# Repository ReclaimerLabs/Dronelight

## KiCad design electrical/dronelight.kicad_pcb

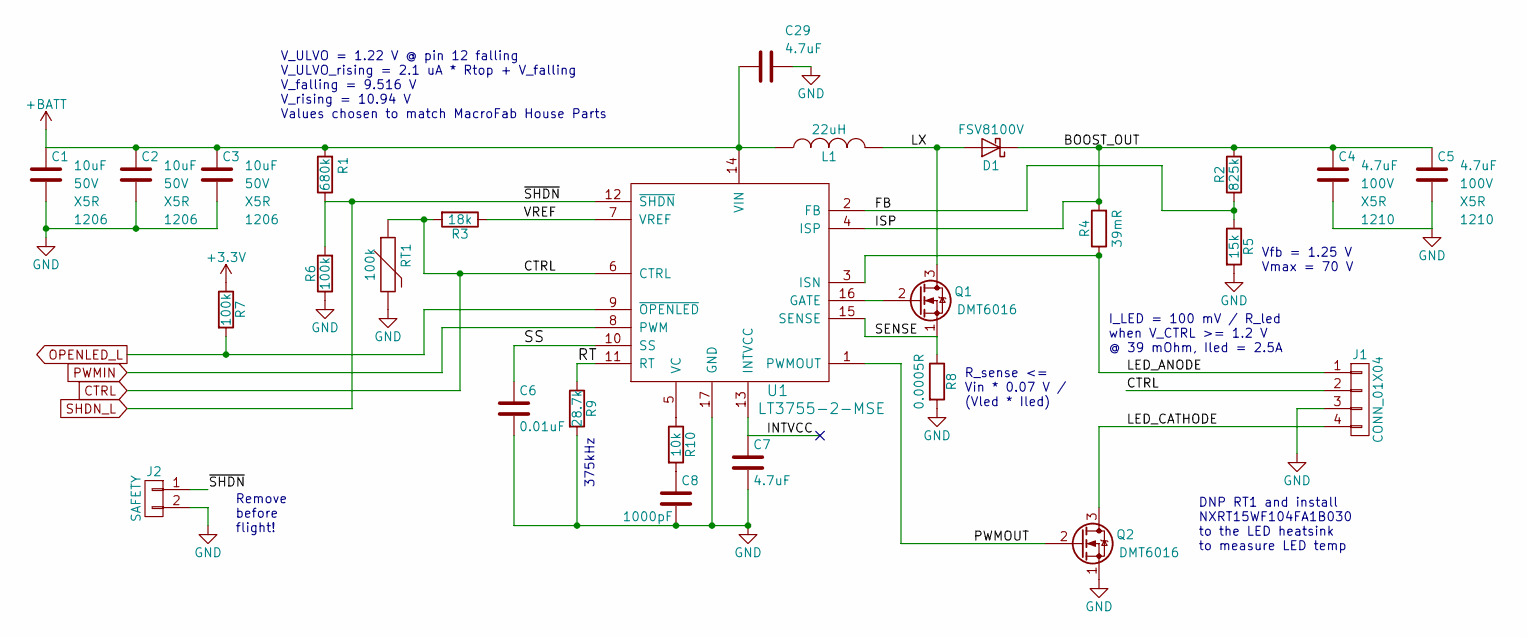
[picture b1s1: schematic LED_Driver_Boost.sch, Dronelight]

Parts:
C1, C2, C3: 10uF; C_1206; Voltage 50V; Manufacturer Part Number CL31A106MBHNNNE
C4, C5: 4.7uF; C_1206; Voltage 100V; Manufacturer Part Number HMK325BJ475KM-PE
C6: 0.01uF; C_0603; Manufacturer Part Number MF-CAP-0603-0.01uF
C7, C29: 4.7uF; C_0805; Manufacturer Part Number CL21A475KOFNNNE
C8: 1000pF; C_0603; Manufacturer Part Number MF-CAP-0603-1nF
D1: FSV8100V; TO-277_3L_Diode; Manufacturer Part Number FSV8100V
J1: CONN_01X04; Header_04x01_2.5mm_RA; Manufacturer Part Number S4B-EH(LF)(SN)
J2: SAFETY; Socket_Strip_Straight_1x02_Pitch2.54mm; Manufacturer Part Number MF-CON-2.54mm-01x02
L1: 22uH; Inductor_DR127; Manufacturer Part Number DR127-220-R
Q1, Q2: DMT6016; POWERDI5060-8; Manufacturer Part Number DMT6016LPS-13
R1: 680k; R_0603; Manufacturer Part Number MF-RES-0603-680K
R2: 825k; R_0603; Manufacturer Part Number MF-RES-0603-825K
R3: 18k; R_0603; Manufacturer Part Number MF-RES-0603-18K
R4: 39mR; R_0603; Manufacturer Part Number ERJ-3BWFR039V
R5: 15k; R_0603; Manufacturer Part Number MF-RES-0603-15K
R6, R7: 100k; R_0603; Manufacturer Part Number MF-RES-0603-100K
R8: 0.0005R; CST0612; Manufacturer Part Number CST0612-FC-R0005-E
R9: 28.7k; R_0603; Manufacturer Part Number ERJ-3EKF2872V
R10: 10k; R_0603; Manufacturer Part Number MF-RES-0603-10K
RT1: 100k; R_0603; Manufacturer Part Number NCP18WF104J03RB
U1: LT3755-2-MSE; MSOP-16-1EP_3x4mm_Pitch0.5mm; Manufacturer Part Number LT3755EMSE-2#PBF

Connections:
+3V3: R7.1; also elsewhere on the board
+BATT: C1.1, C2.1, C3.1, C29.2, L1.1, R1.2, U1.14 (VIN); also elsewhere on the board
/LED Driver Boost/BOOST_OUT: C4.1, C5.1, D1.1 (K), R2.2, R4.2, U1.4 (ISP)
/LED Driver Boost/FB: R2.1, R5.1, U1.2 (FB)
/LED Driver Boost/INTVCC: C7.1, U1.13 (INTVCC)
/LED Driver Boost/LED_ANODE: J1.1, R4.1, U1.3 (ISN)
/LED Driver Boost/LED_CATHODE: J1.4, Q2.3 (D)
/LED Driver Boost/LX: D1.2 (A), L1.2, Q1.3 (D)
/LED Driver Boost/PWMOUT: Q2.2 (G), U1.1 (PWMOUT)
/LED Driver Boost/RT: R9.1, U1.11 (RT)
/LED Driver Boost/SENSE: Q1.1 (S), R8.1, U1.15 (SENSE)
/LED Driver Boost/SS: C6.1, U1.10 (SS)
/LED Driver Boost/VREF: R3.1, U1.7 (VREF)
CTRL: J1.2, R3.2, RT1.1, U1.6 (CTRL); also elsewhere on the board
GND: C1.2, C2.2, C3.2, C4.2, C5.2, C6.2, C7.2, C8.2, C29.1, J1.3, J2.2, Q2.1 (S), R5.2, R6.1, R8.2, R9.2, RT1.2, U1.17 (GND); also elsewhere on the board
unnamed: C8.1, R10.2
unnamed: Q1.2 (G), U1.16 (GATE)
unnamed: R10.1, U1.5 (VC)
OPENLED_L: R7.2, U1.9 (~OPENLED); also elsewhere on the board
PWMIN: U1.8 (PWM); also elsewhere on the board
SHDN_L: J2.1, R1.1, R6.2, U1.12 (~SHDN); also elsewhere on the board

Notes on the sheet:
375kHz
Vfb = 1.25 V Vmax = 70 V
Remove before flight!
V_ULVO = 1.22 V @ pin 12 falling V_ULVO_rising = 2.1 uA * Rtop + V_falling V_falling = 9.516 V V_rising = 10.94 V Values chosen to match MacroFab House Parts
DNP RT1 and install NXRT15WF104FA1B030 to the LED heatsink to measure LED temp
I_LED = 100 mV / R_led when V_CTRL >= 1.2 V @ 39 mOhm, Iled = 2.5A
R_sense <= Vin * 0.07 V / (Vled * Iled)

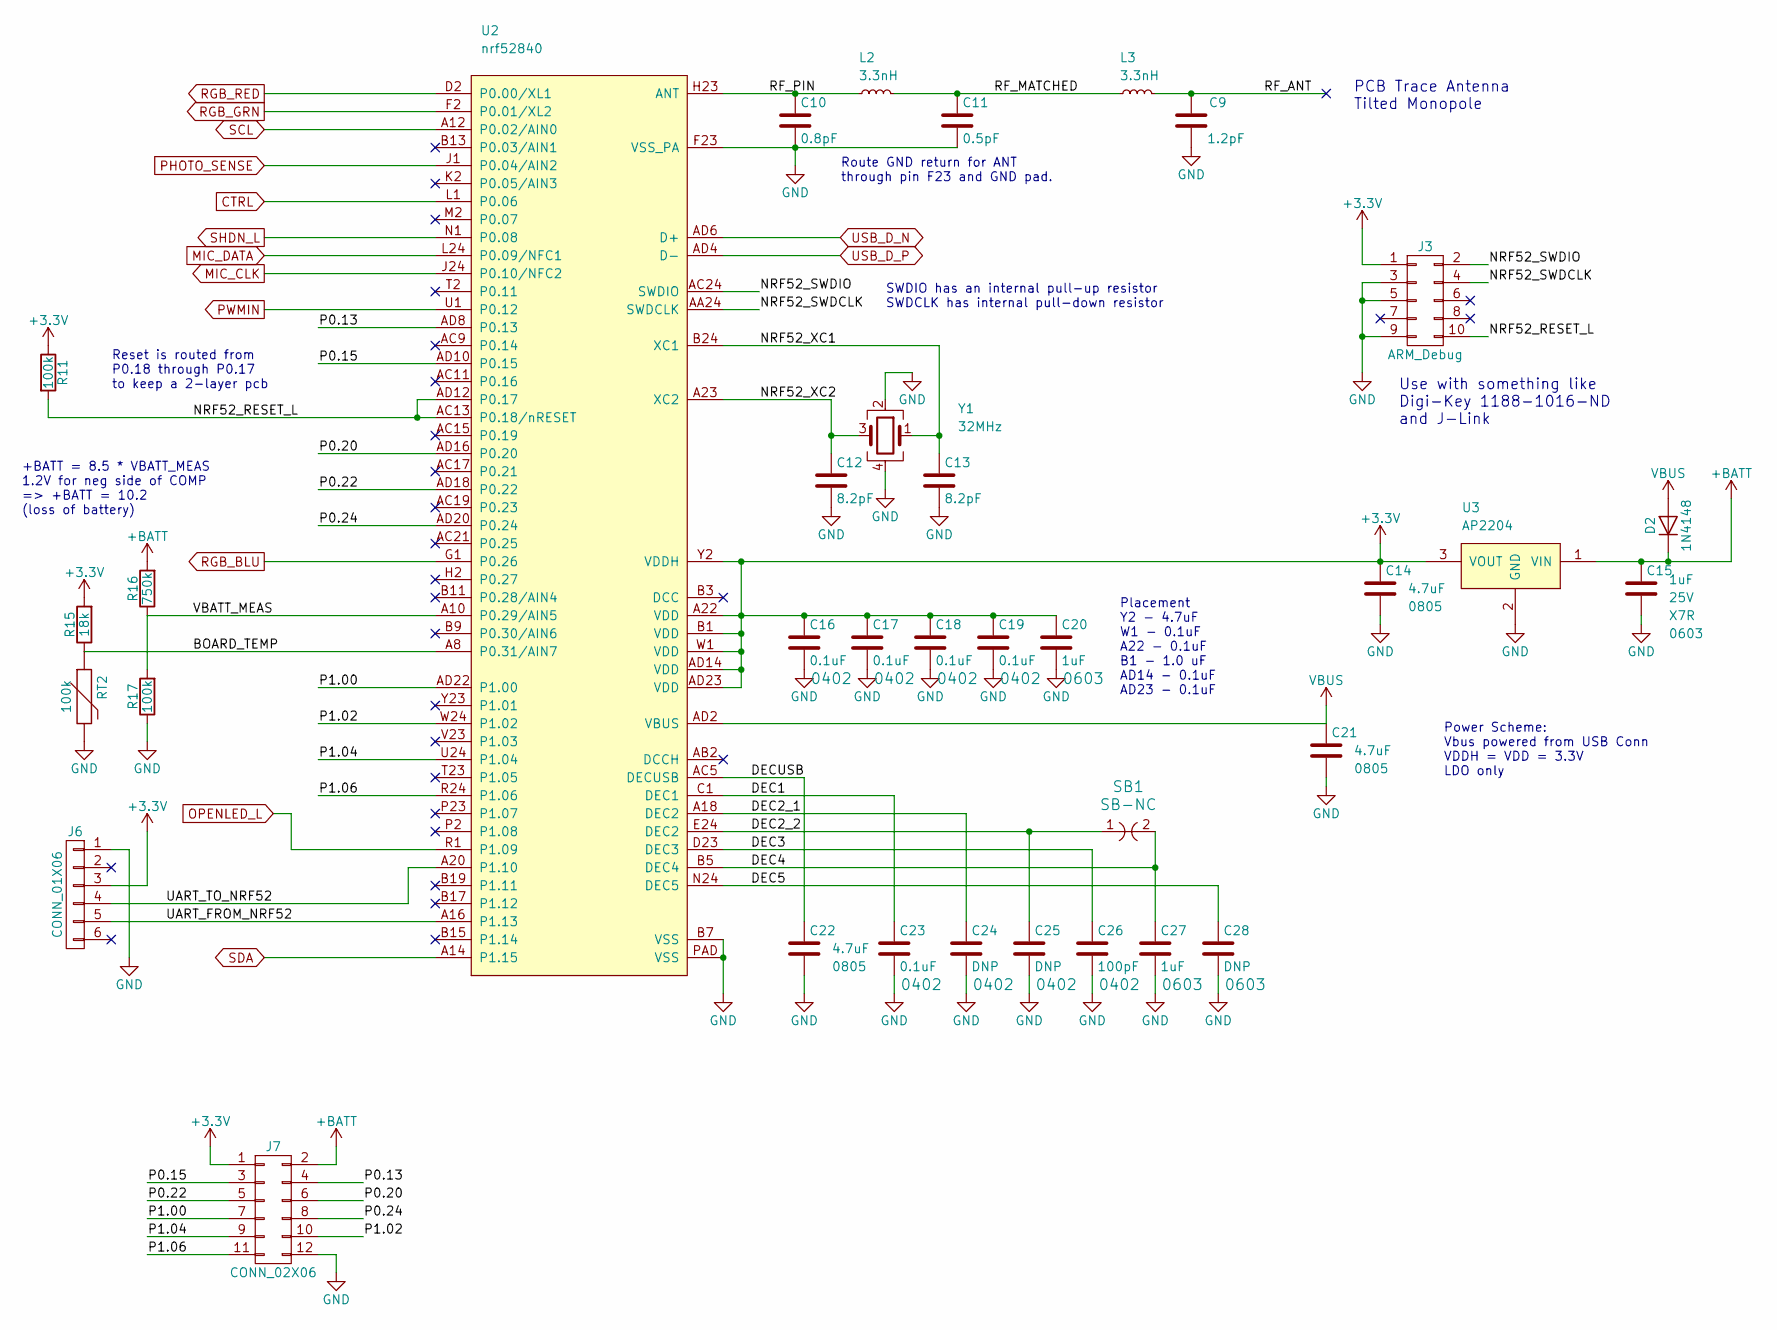
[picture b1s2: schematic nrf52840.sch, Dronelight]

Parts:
C9: 1.2pF; C_0402; Manufacturer Part Number 500R07S1R2BV4T
C10: 0.8pF; C_0402; Manufacturer Part Number GRM1555C2AR80BA01D
C11: 0.5pF; C_0402; Manufacturer Part Number GRM1555C1HR50BA01D
C12, C13: 8.2pF; C_0402; Manufacturer Part Number MF-CAP-0402-8.2pF
C14, C21, C22: 4.7uF; C_0805; Manufacturer Part Number CL21A475KOFNNNE
C15: 1uF; C_0603; Voltage 25V; Manufacturer Part Number MF-CAP-0603-1uF
C16, C17, C18, C19, C23: 0.1uF; C_0402; Manufacturer Part Number MF-CAP-0402-0.1uF
C20, C27: 1uF; C_0603; Manufacturer Part Number MF-CAP-0603-1uF
C24, C25: DNP; C_0402; Manufacturer Part Number MF-CAP-0402-0.1uF
C26: 100pF; C_0402; Manufacturer Part Number GRM1555C1H101JA01D
C28: DNP; C_0603; Manufacturer Part Number MF-CAP-0603-1uF
D2: 1N4148; D_SOD-123; Manufacturer Part Number MF-DIO-SOD123-1N4148
J3: ARM_Debug; HEADER_SMT_02x05_1.27MM_POL; Manufacturer Part Number 3220-10-0300-00
J6: CONN_01X06; Socket_Strip_Straight_1x06_Pitch2.54mm; Manufacturer Part Number MF-CON-2.54mm-01x06
J7: CONN_02X06; Socket_Strip_Straight_2x06_Pitch2.54mm
L2, L3: 3.3nH; C_0402; Manufacturer Part Number MLG1005S3N3BT000
R11, R17: 100k; R_0603; Manufacturer Part Number MF-RES-0603-100K
R15: 18k; R_0603; Manufacturer Part Number MF-RES-0603-18K
R16: 750k; R_0603; Manufacturer Part Number MF-RES-0603-750K
RT2: 100k; R_0603; Manufacturer Part Number NCP18WF104J03RB
SB1: SB-NC
U2: nrf52840; AQFN73; Manufacturer Part Number NRF52840-QIAA-T
U3: AP2204; SOT89-3; Manufacturer Part Number AP2204R-3.3TRG1
Y1: 32MHz; Crystal_SMD_2016-4pin_2.0x1.6mm; Manufacturer Part Number XRCGB32M000F2P00R0

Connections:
+3V3: C14.1, C16.1, C17.1, C18.1, C19.1, C20.1, J3.1, J6.3, J7.1, R11.1, R15.2, U2.A22 (VDD), U2.AD14 (VDD), U2.AD23 (VDD), U2.B1 (VDD), U2.W1 (VDD), U2.Y2 (VDDH), U3.3 (VOUT); also elsewhere on the board
+BATT: C15.1, D2.1 (K), J7.2, R16.2, U3.1 (VIN); also elsewhere on the board
/nrf52840/BOARD_TEMP: R15.1, RT2.1, U2.A8 (P0.31/AIN7)
/nrf52840/DEC1: C23.1, U2.C1 (DEC1)
/nrf52840/DEC2_1: C24.1, U2.A18 (DEC2)
/nrf52840/DEC2_2: C25.1, SB1.1, U2.E24 (DEC2)
/nrf52840/DEC3: C26.1, U2.D23 (DEC3)
/nrf52840/DEC4: C27.1, SB1.2, U2.B5 (DEC4)
/nrf52840/DEC5: C28.1, U2.N24 (DEC5)
/nrf52840/DECUSB: C22.1, U2.AC5 (DECUSB)
/nrf52840/NRF52_RESET_L: J3.10, R11.2, U2.AC13 (P0.18/nRESET), U2.AD12 (P0.17)
/nrf52840/NRF52_SWDCLK: J3.4, U2.AA24 (SWDCLK)
/nrf52840/NRF52_SWDIO: J3.2, U2.AC24 (SWDIO)
/nrf52840/NRF52_XC1: C13.1, U2.B24 (XC1), Y1.1
/nrf52840/NRF52_XC2: C12.1, U2.A23 (XC2), Y1.3
/nrf52840/P0.13: J7.4, U2.AD8 (P0.13)
/nrf52840/P0.15: J7.3, U2.AD10 (P0.15)
/nrf52840/P0.20: J7.6, U2.AD16 (P0.20)
/nrf52840/P0.22: J7.5, U2.AD18 (P0.22)
/nrf52840/P0.24: J7.8, U2.AD20 (P0.24)
/nrf52840/P1.00: J7.7, U2.AD22 (P1.00)
/nrf52840/P1.02: J7.10, U2.W24 (P1.02)
/nrf52840/P1.04: J7.9, U2.U24 (P1.04)
/nrf52840/P1.06: J7.11, U2.R24 (P1.06)
/nrf52840/RF_ANT: C9.2, L3.2
/nrf52840/RF_MATCHED: C11.1, L2.2, L3.1
/nrf52840/RF_PIN: C10.1, L2.1, U2.H23 (ANT)
/nrf52840/UART_FROM_NRF52: J6.5, U2.A16 (P1.13)
/nrf52840/UART_TO_NRF52: J6.4, U2.A20 (P1.10)
/nrf52840/VBATT_MEAS: R16.1, R17.2, U2.A10 (P0.29/AIN5)
CTRL: U2.L1 (P0.06); also elsewhere on the board
GND: C9.1, C10.2, C11.2, C12.2, C13.2, C14.2, C15.2, C16.2, C17.2, C18.2, C19.2, C20.2, C21.2, C22.2, C23.2, C24.2, C25.2, C26.2, C27.2, C28.2, J3.3, J3.5, J3.9, J6.1, J7.12, R17.1, RT2.2, U2.B7 (VSS), U2.F23 (VSS_PA), U2.PAD (VSS), U3.2 (GND), Y1.2, Y1.4; also elsewhere on the board
MIC_CLK: U2.J24 (P0.10/NFC2); also elsewhere on the board
MIC_DATA: U2.L24 (P0.09/NFC1); also elsewhere on the board
OPENLED_L: U2.R1 (P1.09); also elsewhere on the board
PHOTO_SENSE: U2.J1 (P0.04/AIN2); also elsewhere on the board
PWMIN: U2.U1 (P0.12); also elsewhere on the board
RGB_BLU: U2.G1 (P0.26); also elsewhere on the board
RGB_GRN: U2.F2 (P0.01/XL2); also elsewhere on the board
RGB_RED: U2.D2 (P0.00/XL1); also elsewhere on the board
SCL: U2.A12 (P0.02/AIN0); also elsewhere on the board
SDA: U2.A14 (P1.15); also elsewhere on the board
SHDN_L: U2.N1 (P0.08); also elsewhere on the board
USB_D_N: U2.AD6 (D+); also elsewhere on the board
USB_D_P: U2.AD4 (D-); also elsewhere on the board
VBUS: C21.1, D2.2 (A), U2.AD2 (VBUS); also elsewhere on the board

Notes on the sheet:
Use with something like Digi-Key 1188-1016-ND and J-Link
SWDIO has an internal pull-up resistor SWDCLK has internal pull-down resistor
Route GND return for ANT through pin F23 and GND pad.
Placement Y2 - 4.7uF W1 - 0.1uF A22 - 0.1uF B1 - 1.0 uF AD14 - 0.1uF AD23 - 0.1uF
Power Scheme: Vbus powered from USB Conn VDDH = VDD = 3.3V LDO only
+BATT = 8.5 * VBATT_MEAS 1.2V for neg side of COMP => +BATT = 10.2 (loss of battery)
Reset is routed from P0.18 through P0.17 to keep a 2-layer pcb
PCB Trace Antenna Tilted Monopole

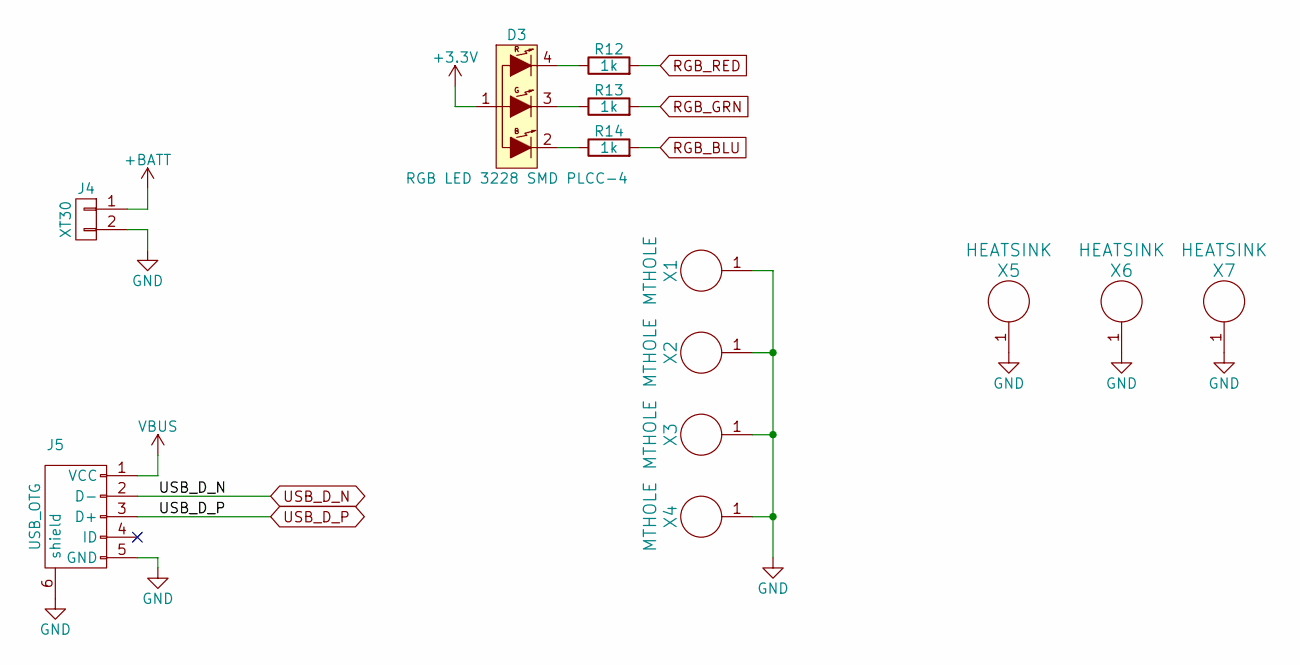
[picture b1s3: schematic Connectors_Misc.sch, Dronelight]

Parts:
D3: RGB LED 3228 SMD PLCC-4; PLCC4; Manufacturer Part Number MF-LED-3228-RGB
J4: XT30
J5: USB_OTG; USB_Micro-B_10118194-0001LF; Manufacturer Part Number MF-CON-MICROUSB-RIGHT
R12, R13, R14: 1k; R_0603; Manufacturer Part Number MF-RES-0603-1K
X1, X2, X3, X4: MTHOLE; MountingHole_3.5mm_Pad_Via
X5, X6, X7: HEATSINK; 573100D00010G; Manufacturer Part Number 573100D00010G

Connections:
+3V3: D3.1; also elsewhere on the board
+BATT: J4.1; also elsewhere on the board
GND: J4.2, J5.5 (GND), J5.6 (shield), X1.1, X2.1, X3.1, X4.1, X5.1, X6.1, X7.1; also elsewhere on the board
unnamed: D3.2 (B), R14.1
unnamed: D3.3 (G), R13.1
unnamed: D3.4 (R), R12.1
RGB_BLU: R14.2; also elsewhere on the board
RGB_GRN: R13.2; also elsewhere on the board
RGB_RED: R12.2; also elsewhere on the board
USB_D_N: J5.2 (D-); also elsewhere on the board
USB_D_P: J5.3 (D+); also elsewhere on the board
VBUS: J5.1 (VCC); also elsewhere on the board

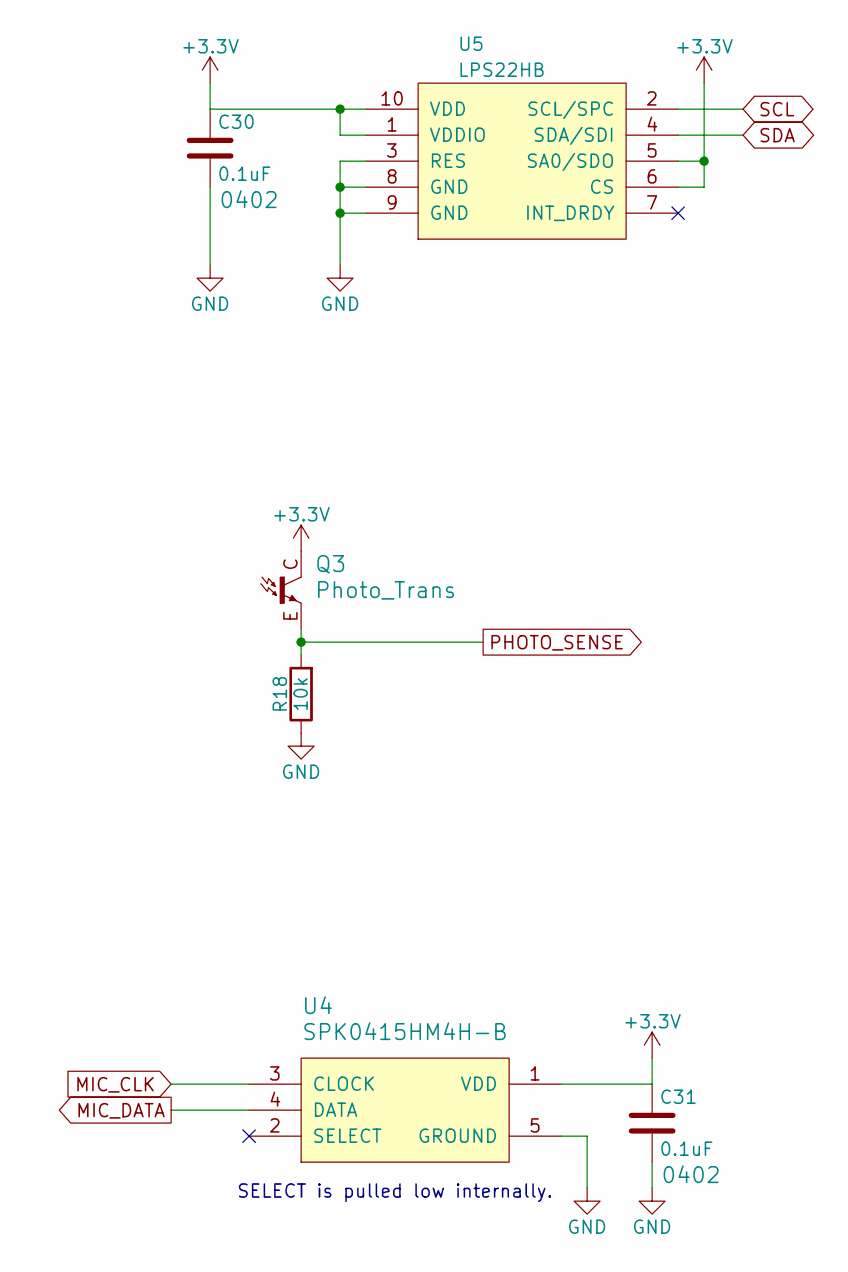
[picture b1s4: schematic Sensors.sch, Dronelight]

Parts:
C30, C31: 0.1uF; C_0402; Manufacturer Part Number MF-CAP-0402-0.1uF
Q3: Photo_Trans; Photo_Trans_ALS-PT19-315C; Manufacturer Part Number ALS-PT19-315C/L177/TR8
R18: 10k; R_0603; Manufacturer Part Number MF-RES-0603-10K
U4: SPK0415HM4H-B; SPK0415HM4H-8; Manufacturer Part Number SPK0415HM4H-B-7
U5: LPS22HB; LGA10R50P2X3_200X200X80; Manufacturer Part Number LPS22HBTR

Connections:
+3V3: C30.1, C31.1, Q3.C, U4.1 (VDD), U5.1 (VDDIO), U5.5 (SA0/SDO), U5.6 (CS), U5.10 (VDD); also elsewhere on the board
GND: C30.2, C31.2, R18.1, U4.5 (GROUND), U5.3 (RES), U5.8 (GND), U5.9 (GND); also elsewhere on the board
MIC_CLK: U4.3 (CLOCK); also elsewhere on the board
MIC_DATA: U4.4 (DATA); also elsewhere on the board
PHOTO_SENSE: Q3.E, R18.2; also elsewhere on the board
SCL: U5.2 (SCL/SPC); also elsewhere on the board
SDA: U5.4 (SDA/SDI); also elsewhere on the board

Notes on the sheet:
SELECT is pulled low internally.

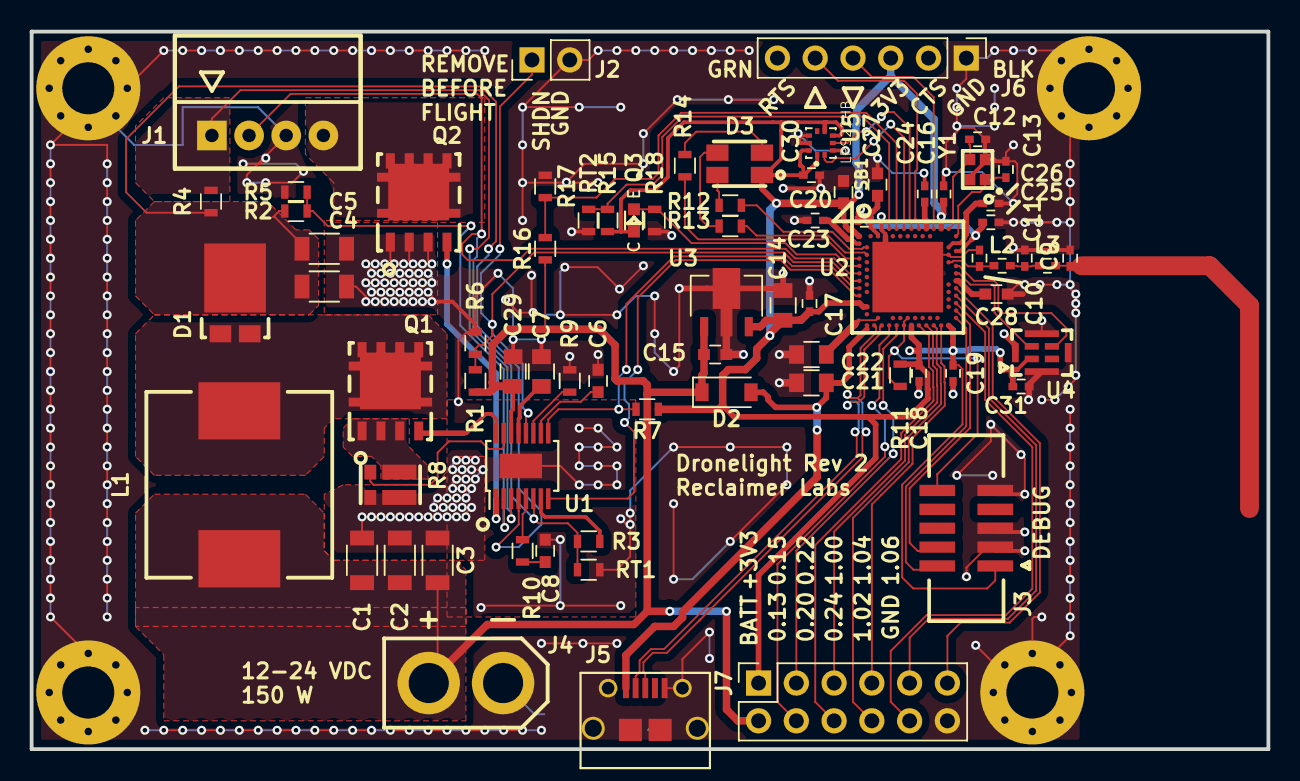
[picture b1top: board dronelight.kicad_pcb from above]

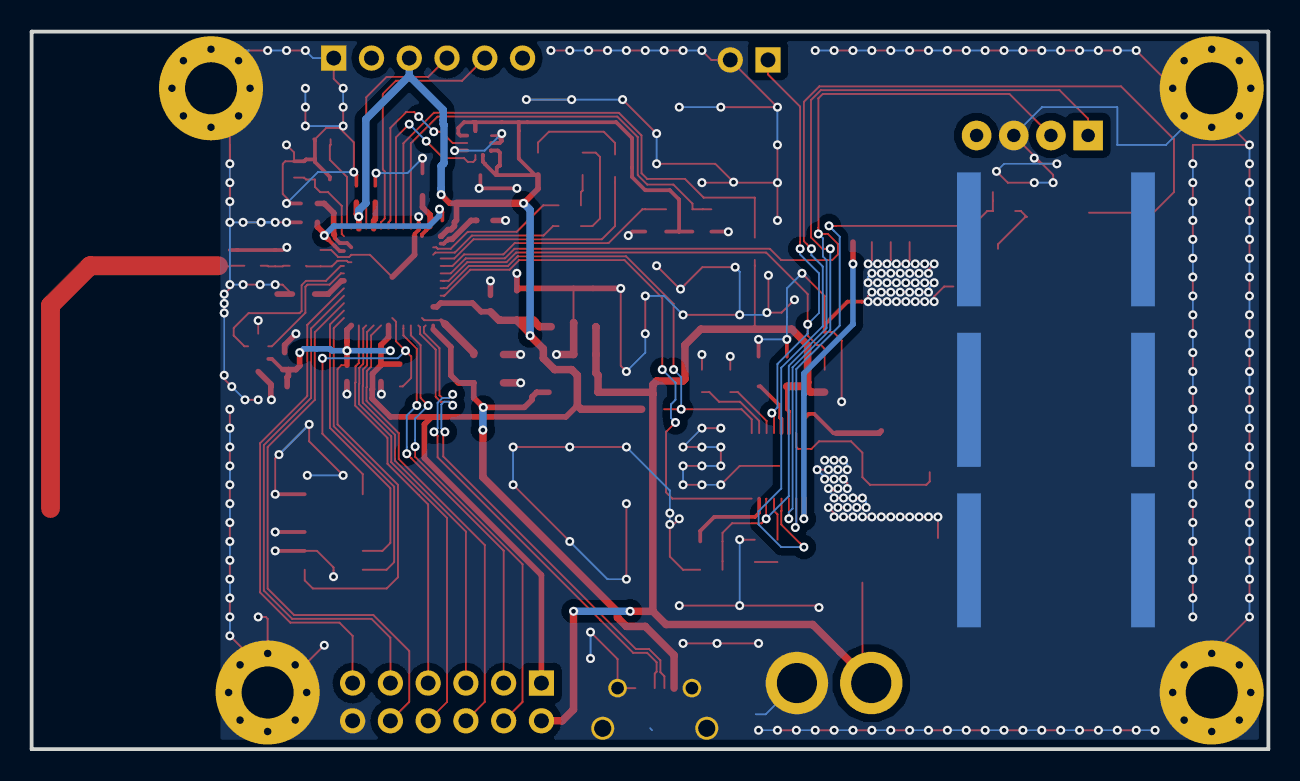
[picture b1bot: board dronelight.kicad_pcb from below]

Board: 2 copper layers, 83.2 x 48.3 mm, 81 parts (3 on the bottom side), 63 nets.

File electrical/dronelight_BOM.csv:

Reference, Value, Footprint, Datasheet, Manufacturer, Manufacturer Part Number, Supplier 1, Supplier 1 Part Number, Voltage, DisplayFootprint, TempCo, DNP
"D1","FSV8100V","Reclaimer_Labs:TO-277_3L_Diode","","Fairchild-ON","FSV8100V","Digikey","FSV8100VCT-ND","","","",""
"L1","22uH","Reclaimer_Labs:Inductor_DR127","","Eaton","DR127-220-R","Digikey","513-1044-1-ND","","","",""
"U1","LT3755-2-MSE","Housings_SSOP:MSOP-16-1EP_3x4mm_Pitch0.5mm","","Linear","LT3755EMSE-2#PBF","Digikey","LT3755EMSE-2#PBF-ND","","","",""
"Q1","DMT6016","Reclaimer_Labs:POWERDI5060-8","","Diodes Inc","DMT6016LPS-13","","","","","",""
"R8","0.0005R","Reclaimer_Labs:CST0612","","Bourns","CST0612-FC-R0005-E","","","","","",""
"C7","4.7uF","Capacitors_SMD:C_0805","","Samsung","CL21A475KOFNNNE","","","","","",""
"C8","1000pF","Capacitors_SMD:C_0603","","MacroFab","MF-CAP-0603-1nF","","","","","",""
"R9","28.7k","Resistors_SMD:R_0603","","Panasonic","ERJ-3EKF2872V","Digikey","P28.7KHCT-ND","","","",""
"C6","0.01uF","Capacitors_SMD:C_0603","","MacroFab","MF-CAP-0603-0.01uF","","","","","",""
"R7","100k","Resistors_SMD:R_0603","","MacroFab","MF-RES-0603-100K","","","","","",""
"RT1","100k","Resistors_SMD:R_0603","","Murata","NCP18WF104J03RB","Digikey","490-2430-1-ND","","","",""
"R3","18k","Resistors_SMD:R_0603","","MacroFab","MF-RES-0603-18K","","","","","",""
"R6","100k","Resistors_SMD:R_0603","","MacroFab","MF-RES-0603-100K","","","","","",""
"R1","680k","Resistors_SMD:R_0603","","MacroFab","MF-RES-0603-680K","","","","","",""
"C3","10uF","Capacitors_SMD:C_1206","","Samsung","CL31A106MBHNNNE","","","50V","1206","X5R",""
"R10","10k","Resistors_SMD:R_0603","","MacroFab","MF-RES-0603-10K","","","","","",""
"R2","825k","Resistors_SMD:R_0603","","MacroFab","MF-RES-0603-825K","","","","","",""
"R4","39mR","Resistors_SMD:R_0603","","Panasonic","ERJ-3BWFR039V","","","","","",""
"R5","15k","Resistors_SMD:R_0603","","MacroFab","MF-RES-0603-15K","","","","","",""
"J2","SAFETY","Socket_Strips:Socket_Strip_Straight_1x02_Pitch2.54mm","","MacroFab","MF-CON-2.54mm-01x02","","","","","",""
"J1","CONN_01X04","Reclaimer_Labs:Header_04x01_2.5mm_RA","","JST","S4B-EH(LF)(SN)","","","","","",""
"C2","10uF","Capacitors_SMD:C_1206","","Samsung","CL31A106MBHNNNE","","","50V","1206","X5R",""
"C1","10uF","Capacitors_SMD:C_1206","","Samsung","CL31A106MBHNNNE","","","50V","1206","X5R",""
"C4","4.7uF","Capacitors_SMD:C_1206","","Taiyo Yuden","HMK325BJ475KM-PE","","","100V","1210","X5R",""
"C5","4.7uF","Capacitors_SMD:C_1206","","Taiyo Yuden","HMK325BJ475KM-PE","","","100V","1210","X5R",""
"Q2","DMT6016","Reclaimer_Labs:POWERDI5060-8","","Diodes Inc","DMT6016LPS-13","","","","","",""
"C29","4.7uF","Capacitors_SMD:C_0805","","Samsung","CL21A475KOFNNNE","","","","","",""
"U2","nrf52840","Reclaimer_Labs:AQFN73","","Nordic","NRF52840-QIAA-T","","","","","",""
"J3","ARM_Debug","Reclaimer_Labs:HEADER_SMT_02x05_1.27MM_POL","","CNC Tech","3220-10-0300-00","","","","","",""
"R11","100k","Resistors_SMD:R_0603","","MacroFab","MF-RES-0603-100K","","","","","",""
"Y1","32MHz","Reclaimer_Labs:Crystal_SMD_2016-4pin_2.0x1.6mm","","Murata","XRCGB32M000F2P00R0","","","","","",""
"C12","8.2pF","Capacitors_SMD:C_0402","","MacroFab","MF-CAP-0402-8.2pF","","","","","",""
"C13","8.2pF","Capacitors_SMD:C_0402","","MacroFab","MF-CAP-0402-8.2pF","","","","","",""
"C10","0.8pF","Capacitors_SMD:C_0402","","Murata","GRM1555C2AR80BA01D","","","","","",""
"L2","3.3nH","Capacitors_SMD:C_0402","","TDK","MLG1005S3N3BT000","","","","","",""
"C11","0.5pF","Capacitors_SMD:C_0402","","Murata","GRM1555C1HR50BA01D","","","","","",""
"D2","1N4148","Diodes_SMD:D_SOD-123","","MacroFab","MF-DIO-SOD123-1N4148","","","","","",""
"C15","1uF","Capacitors_SMD:C_0603","","MacroFab","MF-CAP-0603-1uF","","","25V","0603","X7R",""
"U3","AP2204","Reclaimer_Labs:SOT89-3","","Diodes Inc","AP2204R-3.3TRG1","","","","","",""
"C16","0.1uF","Capacitors_SMD:C_0402","","MacroFab","MF-CAP-0402-0.1uF","","","","0402","",""
"C20","1uF","Capacitors_SMD:C_0603","","MacroFab","MF-CAP-0603-1uF","","","","0603","",""
"C17","0.1uF","Capacitors_SMD:C_0402","","MacroFab","MF-CAP-0402-0.1uF","","","","0402","",""
"C18","0.1uF","Capacitors_SMD:C_0402","","MacroFab","MF-CAP-0402-0.1uF","","","","0402","",""
"C19","0.1uF","Capacitors_SMD:C_0402","","MacroFab","MF-CAP-0402-0.1uF","","","","0402","",""
"C23","0.1uF","Capacitors_SMD:C_0402","","MacroFab","MF-CAP-0402-0.1uF","","","","0402","",""
"C26","100pF","Capacitors_SMD:C_0402","","Murata","GRM1555C1H101JA01D","","","","0402","",""
"C27","1uF","Capacitors_SMD:C_0603","","MacroFab","MF-CAP-0603-1uF","","","","0603","",""
"C24","DNP","Capacitors_SMD:C_0402","","MacroFab","MF-CAP-0402-0.1uF","","","","0402","","DNP"
"C25","DNP","Capacitors_SMD:C_0402","","MacroFab","MF-CAP-0402-0.1uF","","","","0402","","DNP"
"A1","Antenna","Reclaimer_Labs:2450AT18B100E","","Johanson","2450AT18B100E","","","","","",""
"L3","3.3nH","Capacitors_SMD:C_0402","","TDK","MLG1005S3N3BT000","","","","","",""
"C9","1.2pF","Capacitors_SMD:C_0402","","Johanson","500R07S1R2BV4T","","","","","",""
"L4","2.7nH","Capacitors_SMD:C_0402","","Johanson","L-07C2N7SV6T","","","","","",""
"J6","CONN_01X06","Socket_Strips:Socket_Strip_Straight_1x06_Pitch2.54mm","","MacroFab","MF-CON-2.54mm-01x06","","","","","",""
"C21","4.7uF","Capacitors_SMD:C_0805","","Samsung","CL21A475KOFNNNE","","","","0805","",""
"C14","4.7uF","Capacitors_SMD:C_0805","","Samsung","CL21A475KOFNNNE","","","","0805","",""
"C22","4.7uF","Capacitors_SMD:C_0805","","Samsung","CL21A475KOFNNNE","","","","0805","",""
"RT2","100k","Resistors_SMD:R_0603","","Murata","NCP18WF104J03RB","Digikey","490-2430-1-ND","","","",""
"R15","18k","Resistors_SMD:R_0603","","MacroFab","MF-RES-0603-18K","","","","","",""
"R16","750k","Resistors_SMD:R_0603","","MacroFab","MF-RES-0603-750K","","","","","",""
"R17","100k","Resistors_SMD:R_0603","","MacroFab","MF-RES-0603-100K","","","","","",""
"J7","CONN_02X06","Socket_Strips:Socket_Strip_Straight_2x06_Pitch2.54mm",""
"C28","DNP","Capacitors_SMD:C_0603","","MacroFab","MF-CAP-0603-1uF","","","","0603","","DNP"
"J4","XT30","Reclaimer_Labs:XT30",""
"J5","USB_OTG","Reclaimer_Labs:USB_Micro-B_10118194-0001LF","","MacroFab","MF-CON-MICROUSB-RIGHT","","","","","",""
"X1","MTHOLE","Reclaimer_Labs:MountingHole_3.5mm_Pad_Via",""
"R12","1k","Resistors_SMD:R_0603","","MacroFab","MF-RES-0603-1K","","","","","",""
"D3","RGB LED 3228 SMD PLCC-4","Reclaimer_Labs:PLCC4","","MacroFab","MF-LED-3228-RGB","","","","","",""
"R13","1k","Resistors_SMD:R_0603","","MacroFab","MF-RES-0603-1K","","","","","",""
"R14","1k","Resistors_SMD:R_0603","","MacroFab","MF-RES-0603-1K","","","","","",""
"X2","MTHOLE","Reclaimer_Labs:MountingHole_3.5mm_Pad_Via",""
"X3","MTHOLE","Reclaimer_Labs:MountingHole_3.5mm_Pad_Via",""
"X4","MTHOLE","Reclaimer_Labs:MountingHole_3.5mm_Pad_Via",""
"X5","HEATSINK","Reclaimer_Labs:573100D00010G","","Aavid Thermalloy","573100D00010G","","","","","",""
"X6","HEATSINK","Reclaimer_Labs:573100D00010G","","Aavid Thermalloy","573100D00010G","","","","","",""
"X7","HEATSINK","Reclaimer_Labs:573100D00010G","","Aavid Thermalloy","573100D00010G","","","","","",""
"Q3","Photo_Trans","Reclaimer_Labs:Photo_Trans_ALS-PT19-315C","","Everlight","ALS-PT19-315C/L177/TR8","","","","","",""
"R18","10k","Resistors_SMD:R_0603","","MacroFab","MF-RES-0603-10K","","","","","",""
"U5","LPS22HB","Reclaimer_Labs:LGA10R50P2X3_200X200X80","","ST","LPS22HBTR","","","","","",""
"C30","0.1uF","Capacitors_SMD:C_0402","","MacroFab","MF-CAP-0402-0.1uF","","","","0402","",""
"U4","SPK0415HM4H-B","Reclaimer_Labs:SPK0415HM4H-8","","Knowles","SPK0415HM4H-B-7","","","","","",""
"C31","0.1uF","Capacitors_SMD:C_0402","","MacroFab","MF-CAP-0402-0.1uF","","","","0402","",""

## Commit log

2016-05-10 :neckbeard: Added .gitattributes & .gitignore files
2016-05-10 Initial Commit
    Initial commit of Rev 1 hardware and software
2017-11-29 Rev 1 redone
